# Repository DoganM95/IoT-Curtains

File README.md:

# IoT-Curtains
Outer facade electric curtains controlled by an esp32/arduino using Blynk
### Curtain controller pcb (wall module below)

- Pinout of screw spots:  

    Pin 5: Motor  
    Pin 4: Motor  
    Pin 3: close curtains  
    Pin 2: open curtains  
    Pin 1: GND  

- shorting pin 1 and pin 2 opens the curtains  
- shorting pin 1 and pin 3 closes the curtains  
- Pinout of female header pins (Wall side):

#### Power

The wall pcb provides power, rated at 3.3 Volts, but drops with increasing current draw.
The esp32 can be powered with a voltage between 2.2V and 3.6V and supposedly draws max 0.26A (Wifi Tx).
The following table contains measurements of voltage, respective to the current drawn at that moment.

<table>
  <tr>
    <td width="30%">
- 0.0A -> 3.31V<br/>  
- 0.1A -> 3.13V<br/>  
- 0.2A -> 2.93V<br/>  
- 0.3A -> 2.74V<br/>  
- 0.4A -> 2.55V<br/>  
- 0.5A -> 2.37V<br/>      
    </td>
    <td width="50%"></td>
  </tr>
</table>

### Hardware setup

- Shorting pins (1 and 2) && (1 and 3) by esp32 happens using AO3401A or AO3400A Mosfet, where esp controls the gate
- Mosfet Gate is connected to esp32 gpio (open/close)
- Mosfet gate is pulled down using a 10 kOhm resistor, connected from gate to ground
- pin 1 is connected to each Mosfet Source/Drain, depending on the diode direction of your mosfet (compare the 2 above in datasheets)
- pin 2/3 are each connected to a Source/Drain
- gpio will be high for a short time (e.g. 0.5s) to simulate a human button press

#### Existing wall module
This is the controller board that is built in to the wall. The wires of the motors of the facade are routed trough the wall and connected to it using the screw terminals. This module stays as is.
<table>
  <tr>
<td width="50%"></td>
    <td width="50%"></td>
  </tr>
</table>

#### Preview of retrofitting smart module
This is the smart-module built in this project, which attaches to the wall-module above. It replaces the simple stock pcb that was attached to the wall module by default and only provided two led's (green/red) and two buttons (open/close).
<table>
  <tr>
<td width="50%"></td>
    <td width="50%"></td>
  </tr>
</table>

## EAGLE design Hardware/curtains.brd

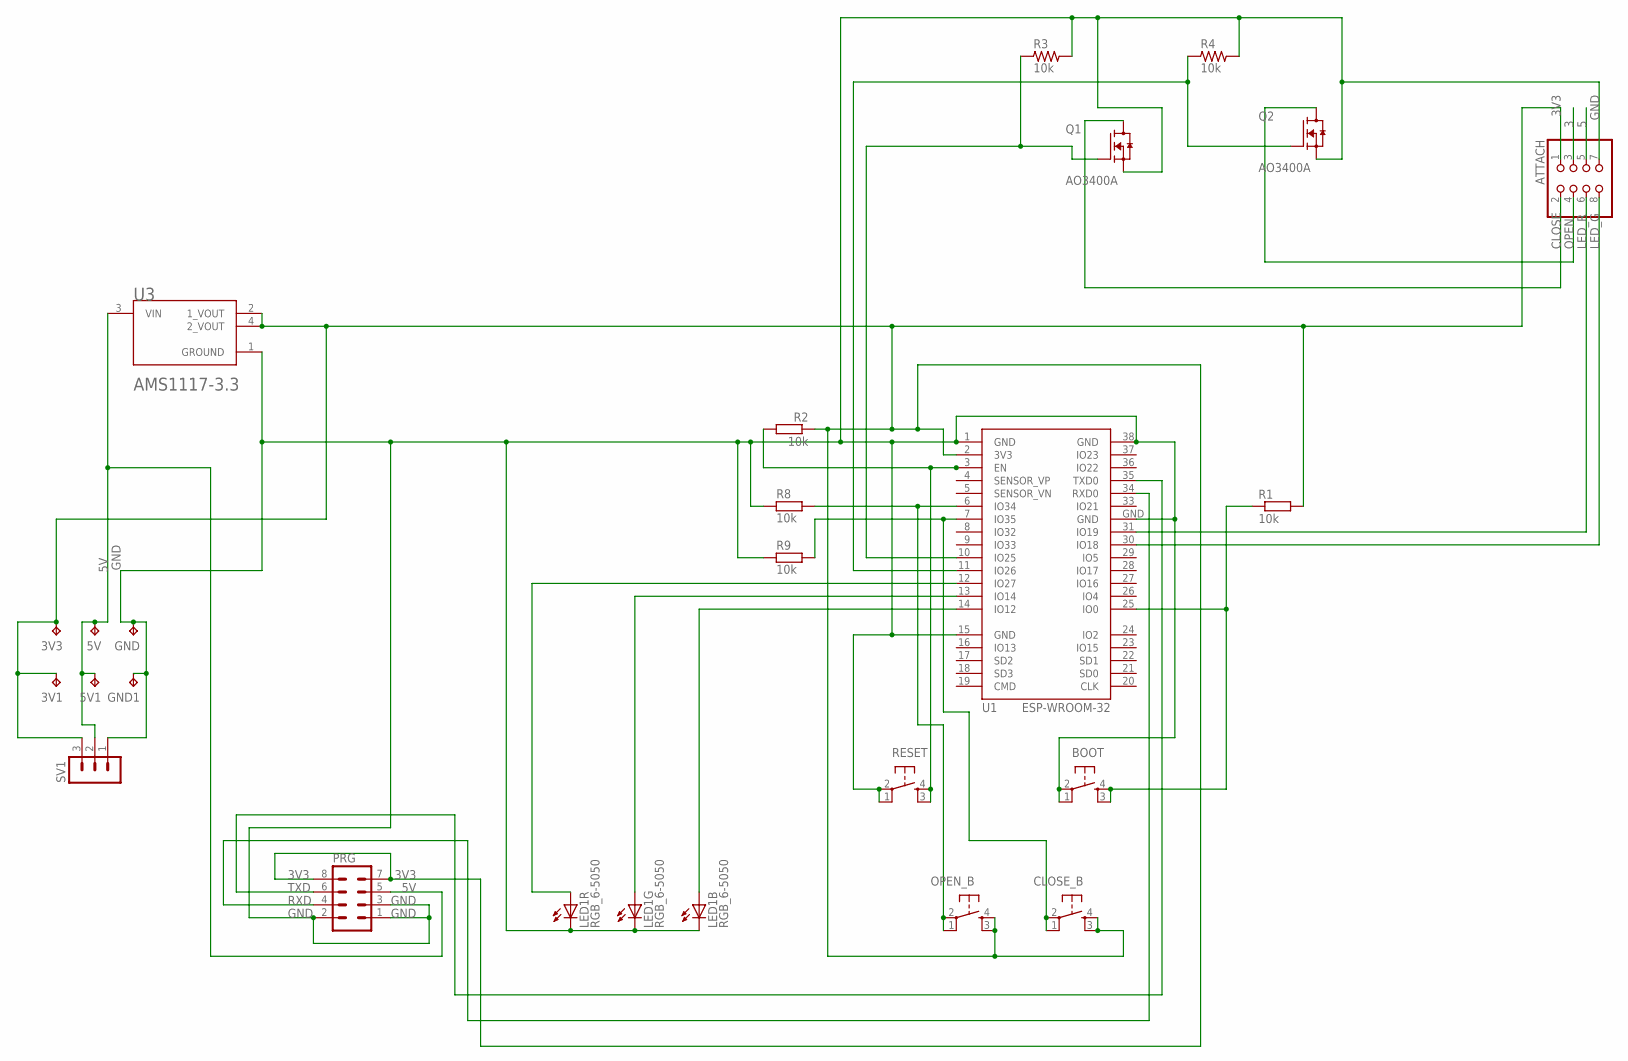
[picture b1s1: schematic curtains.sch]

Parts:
3V1, 3V3, 5V, 5V1: TPB1,27; B1,27
ATTACH: PINHD-2X4; 2X04
BOOT: 10-XX4X4SMD; BT4X4
CLOSE_B: 10-XX4X4SMD; BT4X4
GND, GND1: TPB1,27; B1,27
LED1: RGB_6-5050; 5050_PLCC6
OPEN_B: 10-XX4X4SMD; BT4X4
PRG: MA04-2
Q1, Q2: AO3400A; SOT95P280X125-3N
R1, R2, R8, R9: 10k; R0603
R3, R4: 10k; RC-MASTER-SMD_R0603MP
RESET: 10-XX4X4SMD; BT4X4
SV1: MA03-1
U1: ESP-WROOM-32
U3: ADVANCED_MONOLITHIC_SYSTEMS_AMS1117-3.3ADVANCED_M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; ADVANCED_MONOLITHIC_SYSTEMS_AMS1117-3.3_0

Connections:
3: ATTACH.3
3V3: 3V1.TP, 3V3.TP, ATTACH.1, CLOSE_B.3 (S1), CLOSE_B.4 (S), OPEN_B.3 (S1), OPEN_B.4 (S), PRG.7, PRG.8, R1.2, R2.1, SV1.3, U1.2 (3V3), U3.2 (1_VOUT), U3.4 (2_VOUT)
5: ATTACH.5
5V: 5V.TP, 5V1.TP, PRG.5, SV1.2, U3.3 (VIN)
CLOSE: ATTACH.2, Q1.3 (D)
GND: ATTACH.7, BOOT.1, BOOT.2, GND.TP, GND1.TP, LED1.4 (C), LED1.5 (C), LED1.6 (C), PRG.1, PRG.2, PRG.3, Q1.2 (S), Q2.2 (S), R3.2, R4.2, R8.1, R9.1, RESET.1, RESET.2, SV1.1, U1.1 (GND), U1.15 (GND), U1.38 (GND), U1.GND, U3.1 (GROUND)
LED_G: ATTACH.8, U1.30 (IO18)
LED_R: ATTACH.6, U1.31 (IO19)
unnamed: BOOT.3 (S1), BOOT.4 (S), R1.1, U1.25 (IO0)
unnamed: OPEN_B.1, OPEN_B.2, R8.2, U1.6 (IO34)
unnamed: R2.2, RESET.3 (S1), RESET.4 (S), U1.3 (EN)
unnamed: Q1.1 (G), R3.1, U1.10 (IO25)
unnamed: Q2.1 (G), R4.1, U1.11 (IO26)
unnamed: LED1.2 (A), U1.13 (IO14)
unnamed: LED1.3 (A), U1.14 (IO12)
unnamed: CLOSE_B.1, CLOSE_B.2, R9.2, U1.7 (IO35)
unnamed: LED1.1 (A), U1.12 (IO27)
OPEN: ATTACH.4, Q2.3 (D)
RXD: PRG.4, U1.34 (RXD0)
TXD: PRG.6, U1.35 (TXD0)

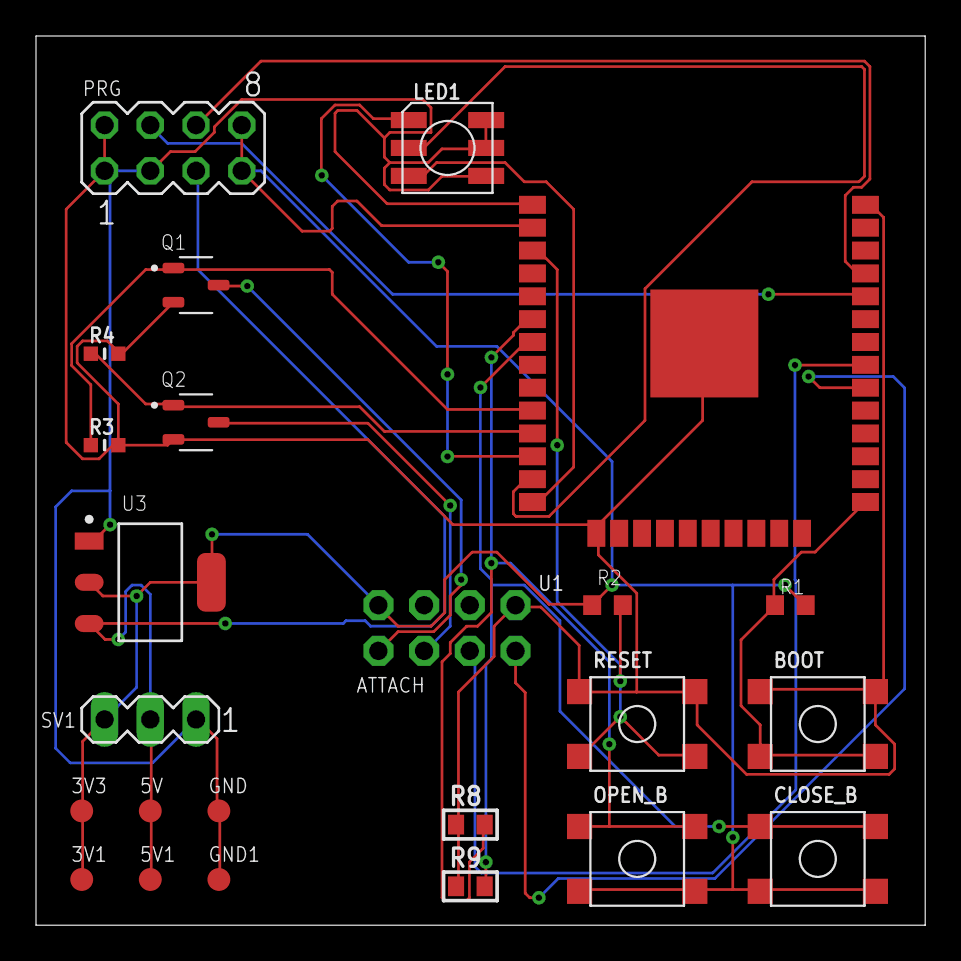
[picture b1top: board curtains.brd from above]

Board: 2 copper layers, 49.4 x 49.4 mm, 24 parts (1 on the bottom side), 18 nets.

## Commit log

2022-05-13 untested initital prototype
2022-05-13 add readme
2022-05-13 fix md typo
2022-05-14 sort by image
2022-05-14 fix setup
2022-06-03 fix for every day use
2022-06-04 logic fix
2022-12-23 add pcb files
2022-12-23 add schematics to readme
2022-12-23 prioritize text
2022-12-23 prioritize schematic
2022-12-23 specify
2022-12-24 add jlcpcb resource
2022-12-24 fix images
2022-12-28 add gerber files from pcb design
2023-01-19 restructure for platformio
2023-01-23 fix dead links
2023-05-06 turn into platformio project
2023-05-31 fix PIO stuff
2023-05-31 add new version images
2023-05-31 add gerber files for v2
2023-06-01 Recreate README.md
2023-06-01 remove unneeded functionality
2023-06-02 add led color func, button sense thread & todos
2023-06-04 implement wall led sensor
2023-06-04 add more led stuff
2023-06-04 fix green led restore bug
2023-06-04 add configurable brightness
2023-06-05 add app controllable brightness
2023-06-05 fix doc
2023-06-05 rm comment
2023-11-10 restructure to have soft and hardware
2023-11-10 cleanup
2023-11-10 move
2023-11-10 add subdir as source
2023-11-10 remove redundant cionfig
2023-11-13 update assets
2023-11-13 add stock module asset

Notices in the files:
parts and their libraries:
rc-master: Copyright (C) 2007, Bob Starr
esp32: Creative Commons Attribution-ShareAlike 4.0 International
